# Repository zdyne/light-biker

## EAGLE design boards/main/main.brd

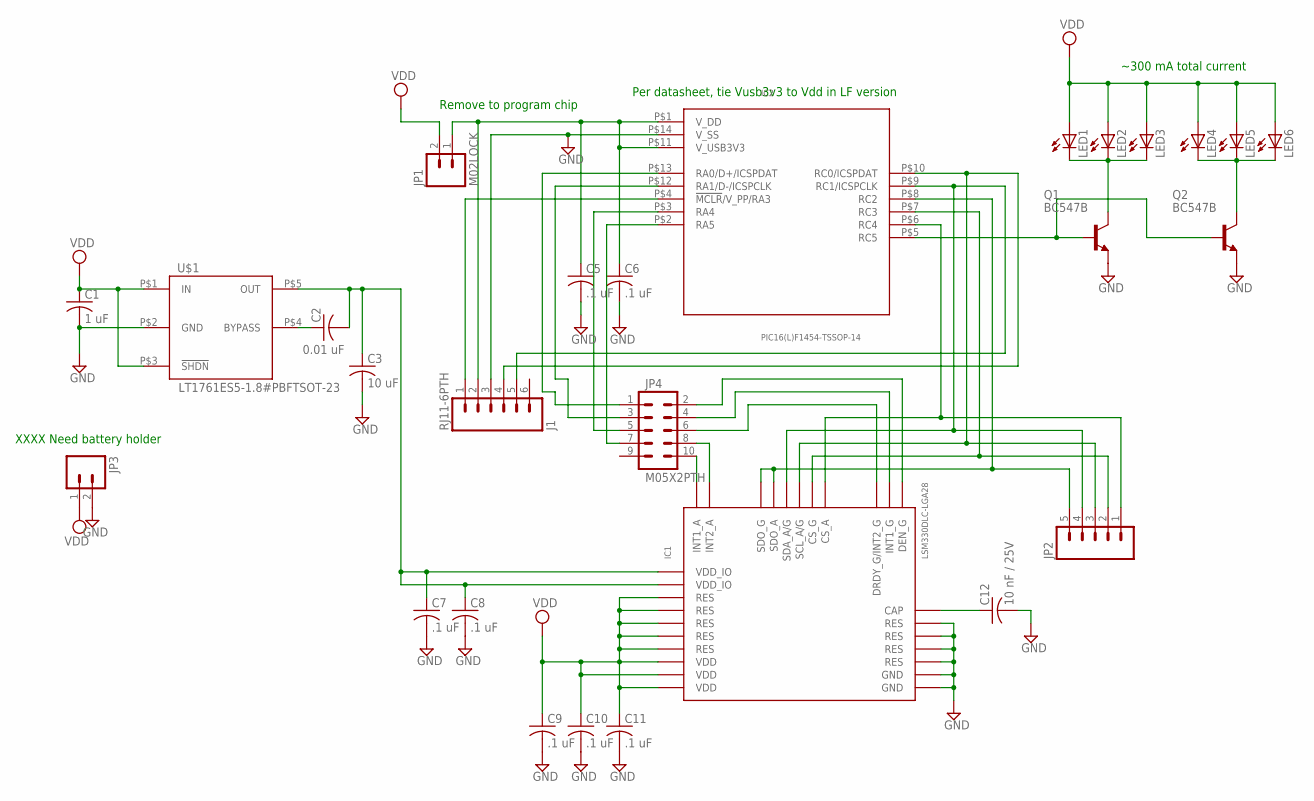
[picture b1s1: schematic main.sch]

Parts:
C1: 1 uF; C1206
C2: 0.01 uF; C1206
C3: 10 uF; C1206
C5, C6, C7, C8, C9, C10, C11: .1 uF; C1206
C12: 10 nF / 25V; C1206
IC1: LSM330DLC-LGA28; LGA-28
IC2: PIC16(L)F1454-TSSOP-14; TSSOP-14
J1: RJ11-6PTH; RJ11-6
JP1, JP3: M02LOCK; 1X02_LOCK
JP2: M05PTH; 1X05
JP4: M05X2PTH; AVR_ICSP
LED1, LED2, LED3, LED4, LED5, LED6: LED5MM
Q1, Q2: BC547B; TO92
U$1: LT1761ES5-1.8#PBFTSOT-23; TSOT-23

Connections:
GND: C1.2, C3.2, C5.2, C6.2, C7.2, C8.2, C9.2, C10.2, C11.2, C12.2, IC1.P$1 (GND), IC1.P$2 (RES), IC1.P$3 (RES), IC1.P$4 (RES), IC1.P$5 (RES), IC1.P$6 (GND), IC2.P$14 (V_SS), J1.3, JP3.2, Q1.1 (E), Q2.1 (E), U$1.P$2 (GND)
unnamed: C2.2, C3.1, C7.1, C8.1, IC1.P$21 (VDD_IO), IC1.P$25 (VDD_IO), U$1.P$5 (OUT)
unnamed: C2.1, U$1.P$4 (BYPASS)
unnamed: IC2.P$4 (!MCLR!/V_PP/RA3), J1.1
unnamed: C5.1, C6.1, IC2.P$1 (V_DD), IC2.P$11 (V_USB3V3), J1.2, JP1.1
unnamed: IC1.P$24 (SCL_A/G), IC2.P$10 (RC0/ICSPDAT), J1.4, JP2.3
unnamed: IC1.P$28 (SDA_A/G), IC2.P$9 (RC1/ICSPCLK), J1.5, JP2.4
unnamed: IC1.P$26 (SDO_G), IC1.P$27 (SDO_A), IC2.P$8 (RC2), JP2.5
unnamed: LED1.K (C), LED2.K (C), LED3.K (C), Q1.3 (C)
unnamed: IC1.P$22 (CS_G), IC2.P$7 (RC3), JP2.2
unnamed: IC1.P$23 (CS_A), IC2.P$6 (RC4), JP2.1
unnamed: LED4.K (C), LED5.K (C), LED6.K (C), Q2.3 (C)
unnamed: IC2.P$5 (RC5), Q1.2 (B), Q2.2 (B)
unnamed: IC2.P$13 (RA0/D+/ICSPDAT), JP4.1
unnamed: IC1.P$20 (INT1_A), JP4.10
unnamed: IC1.P$19 (INT2_A), JP4.8
unnamed: IC1.P$17 (DRDY_G/INT2_G), JP4.6
unnamed: IC1.P$18 (INT1_G), JP4.4
unnamed: IC1.P$16 (DEN_G), JP4.2
unnamed: IC2.P$12 (RA1/D-/ICSPCLK), JP4.3
unnamed: IC2.P$3 (RA4), JP4.5
unnamed: IC2.P$2 (RA5), JP4.7
unnamed: C12.1, IC1.P$15 (CAP)
VDD: C1.1, C9.1, C10.1, C11.1, IC1.P$7 (VDD), IC1.P$8 (VDD), IC1.P$9 (VDD), IC1.P$10 (RES), IC1.P$11 (RES), IC1.P$12 (RES), IC1.P$13 (RES), IC1.P$14 (RES), JP1.2, JP3.1, LED1.A, LED2.A, LED3.A, LED4.A, LED5.A, LED6.A, U$1.P$1 (IN), U$1.P$3 (!SHDN!)

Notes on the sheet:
XXXX Need battery holder
Remove to program chip
Per datasheet, tie Vusb3v3 to Vdd in LF version
~300 mA total current

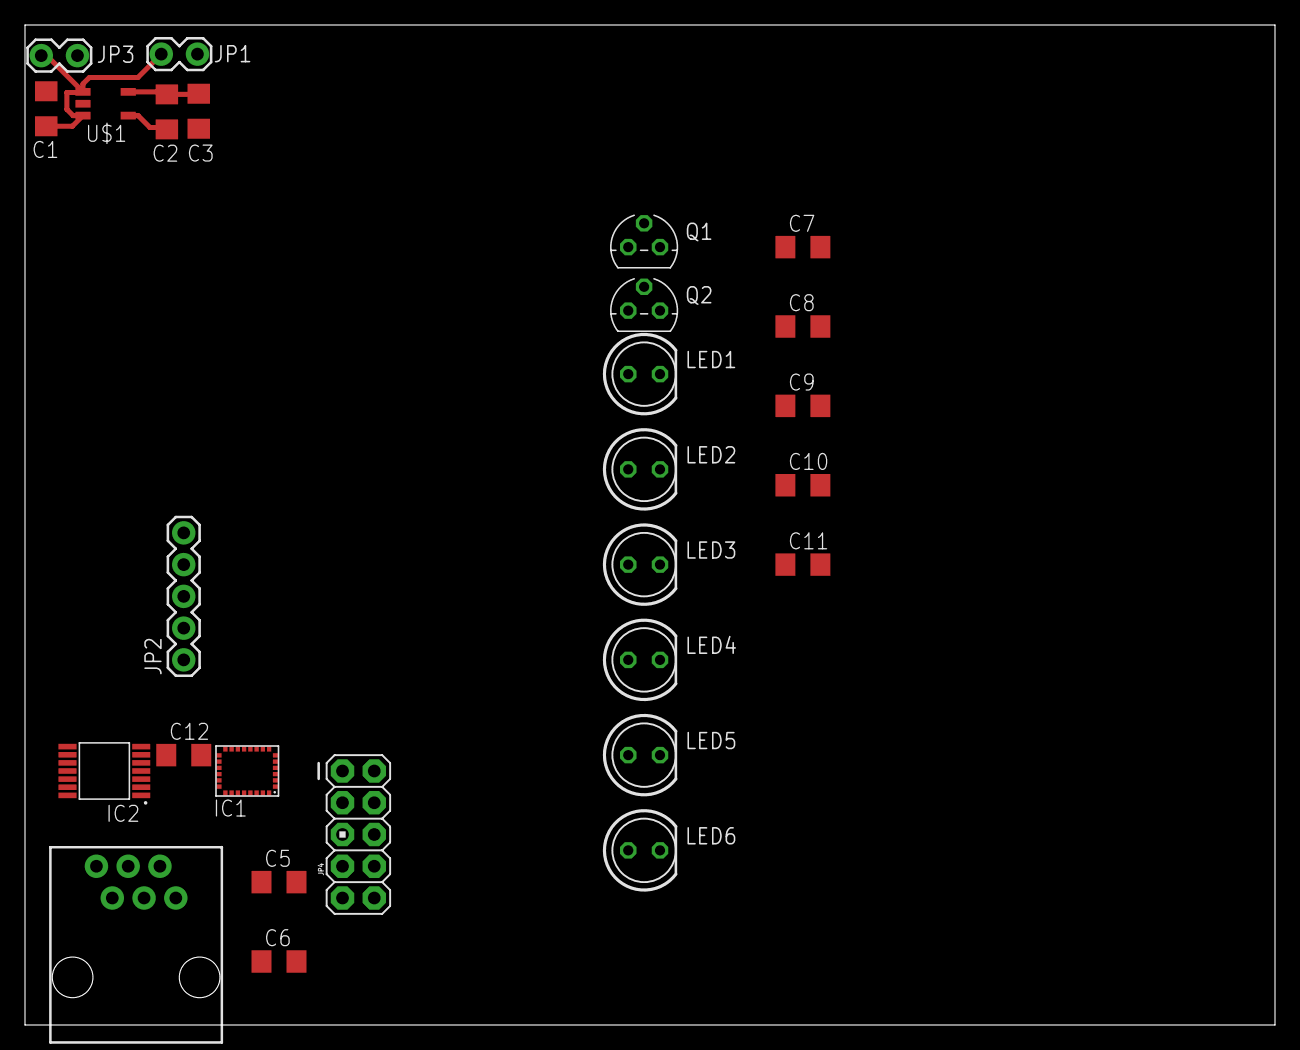
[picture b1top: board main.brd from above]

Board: 2 copper layers, 100.0 x 80.0 mm, 27 parts (0 on the bottom side), 24 nets.

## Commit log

2014-12-24 Added Linear Technology micropower regulator (1.8V) part and schematic.
2014-12-24 Added regulator to layout.

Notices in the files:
parts and their libraries:
SparkFun-Connectors: Licensing: Creative Commons ShareAlike 4.0 International - https://creativecommons.org/licenses/by-sa/4.0
